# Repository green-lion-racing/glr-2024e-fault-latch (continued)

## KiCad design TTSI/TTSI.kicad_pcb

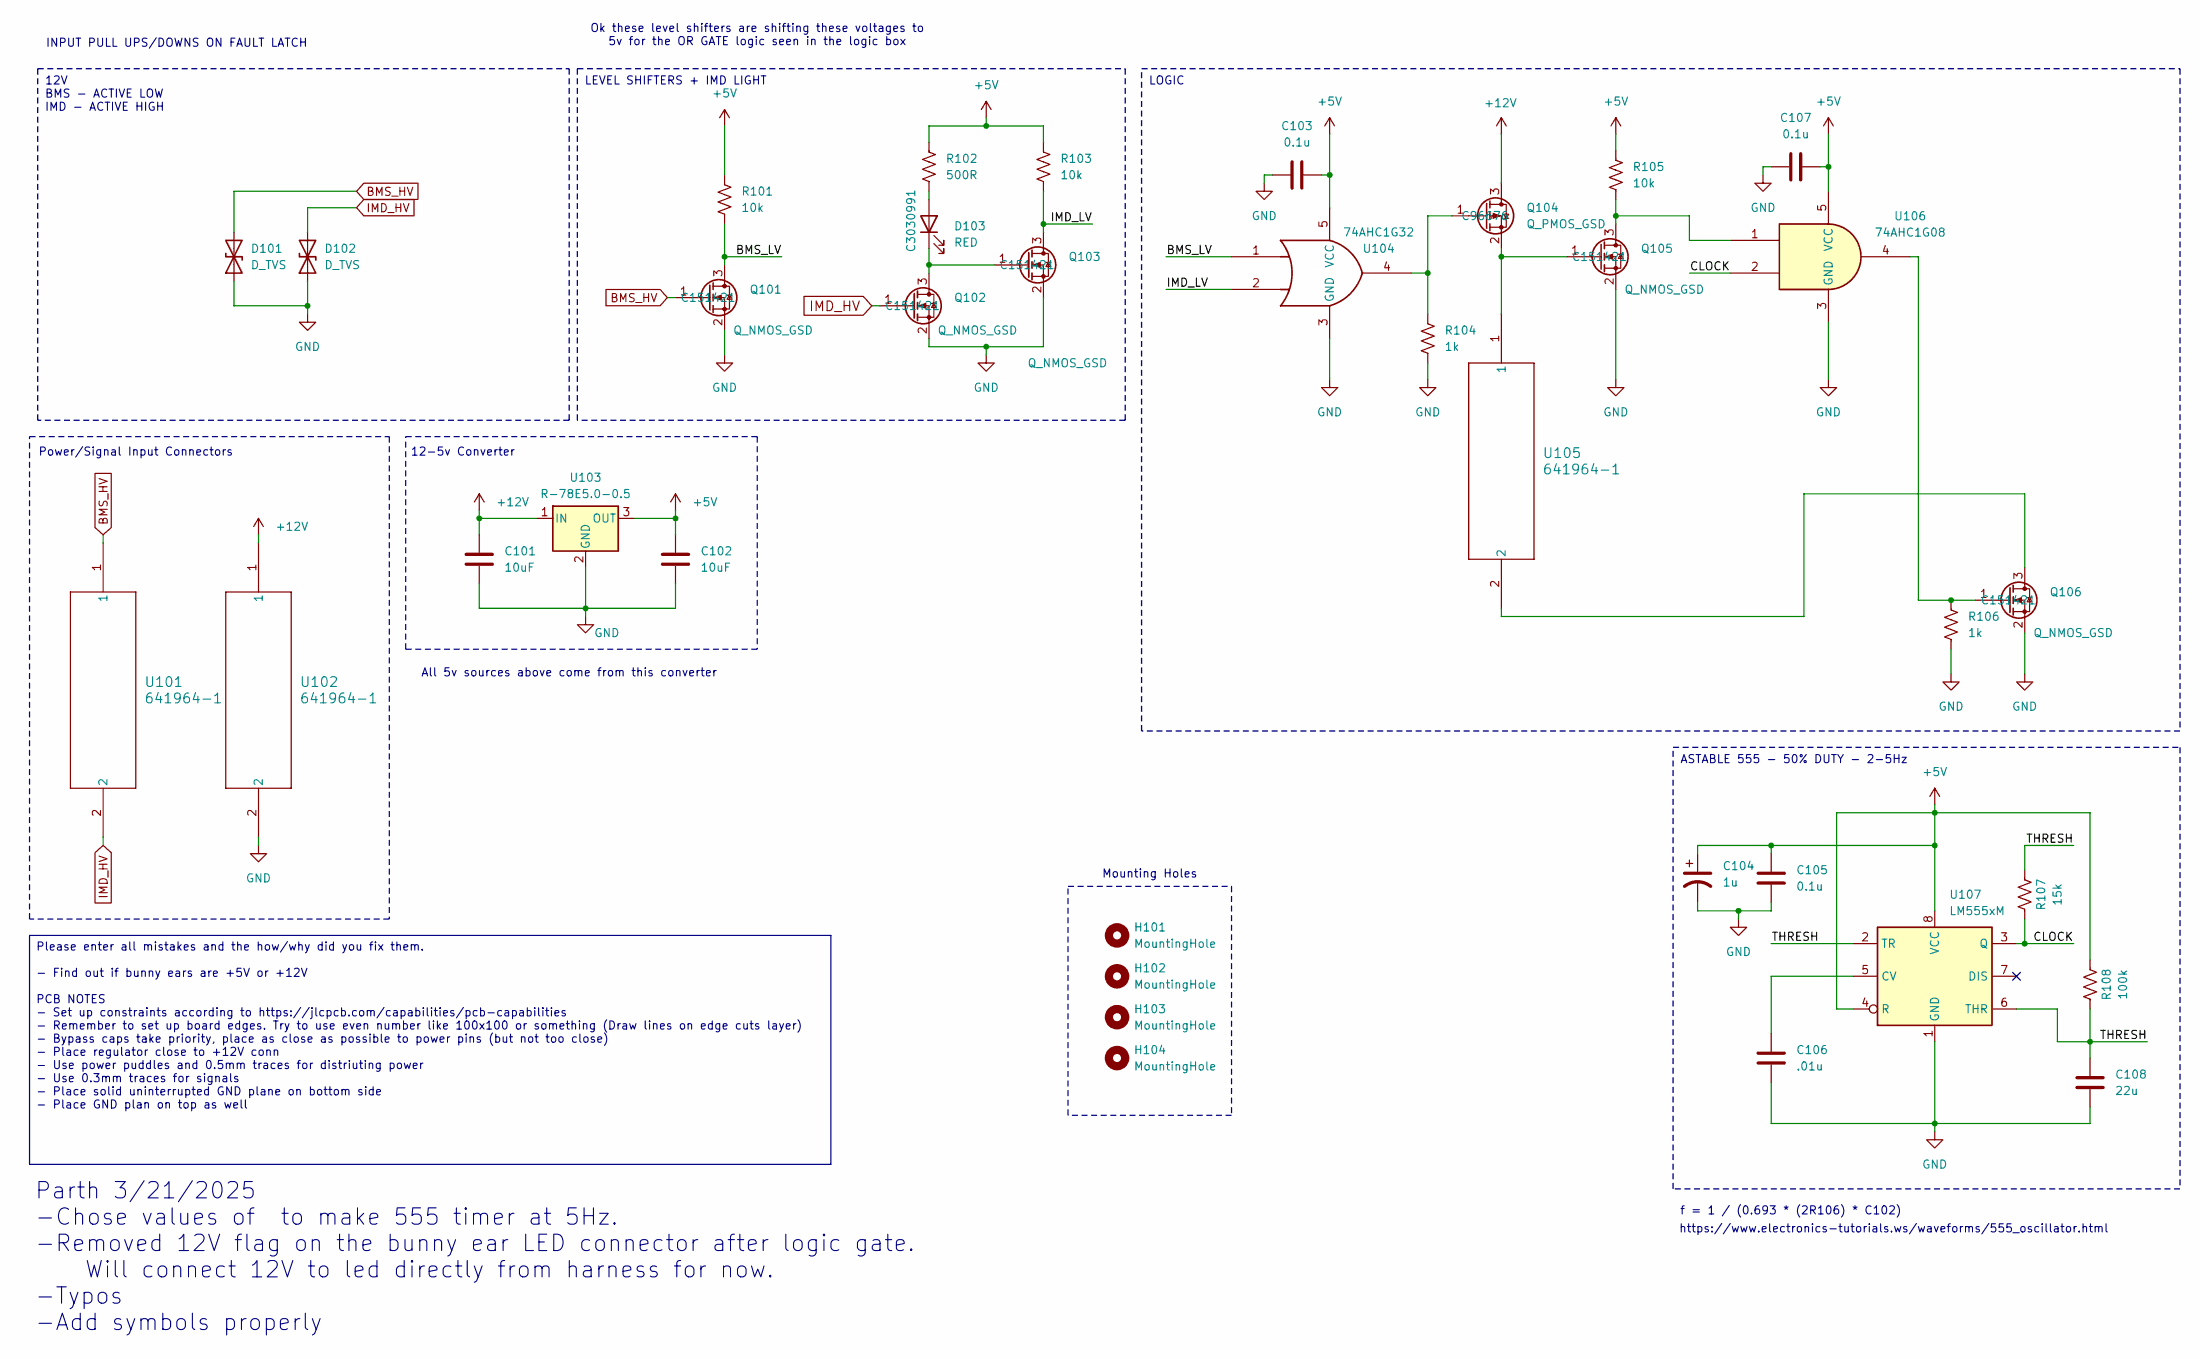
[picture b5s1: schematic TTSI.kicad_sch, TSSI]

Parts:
C101, C102: 10uF; C_0402_1005Metric; JLC# C307520
C103, C105, C107: 0.1u; C_0402_1005Metric; JLC# C133086
C104: 1u; C_0402_1005Metric; JLC# C59782
C106: .01u; C_0402_1005Metric; JLC# C15195
C108: 22u; C_0402_1005Metric
D101, D102: D_TVS; D_SOD-123F; JLC# C110748
D103: RED; R_0603_1608Metric; JLC# C3030991
H101, H102, H103, H104: MountingHole; MountingHole_2.2mm_M2
Q101, Q102, Q103, Q105, Q106: Q_NMOS_GSD; SOT-23; JLC# C151421
Q104: Q_PMOS_GSD; SOT-523; JLC# C96676
R101, R103, R105: 10k; R_0603_1608Metric; JLC# C130232
R102: 500R; R_0603_1608Metric; JLC# C130232
R104, R106: 1k; R_0603_1608Metric; JLC# C105637
R107: 15k; R_0603_1608Metric
R108: 100k; R_0603_1608Metric; JLC# C60491
U101, U102, U105: 641964-1; 641964-1_TYC
U103: R-78E5.0-0.5; R-78E-0.5_RCP; JLC# C5199916
U104: 74AHC1G32; SOT-353_SC-70-5; JLC# C7394028
U106: 74AHC1G08; SOT-353_SC-70-5; JLC# C2861162
U107: LM555xM; SOIC-8_3.9x4.9mm_P1.27mm; JLC# C90760

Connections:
+5V: C102.1, C103.1, C104.1, C105.1, C107.1, R101.1, R102.1, R103.1, R105.1, R108.2, U103.3 (OUT), U104.5 (VCC), U106.5 (VCC), U107.4 (R), U107.8 (VCC)
+12V: C101.1, Q104.3 (D), U102.1, U103.1 (IN)
/BMS_LV: Q101.3 (D), R101.2, U104.1
/CLOCK: R107.1, U106.2, U107.3 (Q)
/IMD_LV: Q103.3 (D), R103.2, U104.2
/THRESH: C108.2, R107.2, R108.1, U107.2 (TR), U107.6 (THR)
BMS_HV: D101.2 (A2), Q101.1 (G), U101.1
GND: C101.2, C102.2, C103.2, C104.2, C105.2, C106.2, C107.2, C108.1, D101.1 (A1), D102.1 (A1), Q101.2 (S), Q102.2 (S), Q103.2 (S), Q105.2 (S), Q106.2 (S), R104.2, R106.2, U102.2, U103.2 (GND), U104.3 (GND), U106.3 (GND), U107.1 (GND)
IMD_HV: D102.2 (A2), Q102.1 (G), U101.2
unnamed: D103.2 (A), R102.2
unnamed: D103.1 (K), Q102.3 (D), Q103.1 (G)
unnamed: Q104.1 (G), R104.1, U104.4
unnamed: Q104.2 (S), Q105.1 (G), U105.1
unnamed: Q105.3 (D), R105.2, U106.1
unnamed: Q106.3 (D), U105.2
unnamed: Q106.1 (G), R106.1, U106.4
unnamed: C106.1, U107.5 (CV)

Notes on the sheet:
Mounting Holes
All 5v sources above come from this converter
f = 1 / (0.693 * (2R106) * C102)
INPUT PULL UPS/DOWNS ON FAULT LATCH
Power/Signal Input Connectors
Parth 3/21/2025 -Chose values of to make 555 timer at 5Hz. -Removed 12V flag on the bunny ear LED connector after logic gate. Will connect 12V to led directly from harness for now. -Typos -Add symbols properly
Ok these level shifters are shifting these voltages to 5v for the OR GATE logic seen in the logic box
12-5v Converter
https://www.electronics-tutorials.ws/waveforms/555_oscillator.html
LEVEL SHIFTERS + IMD LIGHT
ASTABLE 555 - 50% DUTY - 2-5Hz
LOGIC
12V BMS - ACTIVE LOW IMD - ACTIVE HIGH
Please enter all mistakes and the how/why did you fix them. - Find out if bunny ears are +5V or +12V PCB NOTES - Set up constraints according to https://jlcpcb.com/capabilities/pcb-capabilities - Remember to set up board edges. Try to use even number like 100x100 or something (Draw lines on edge cu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

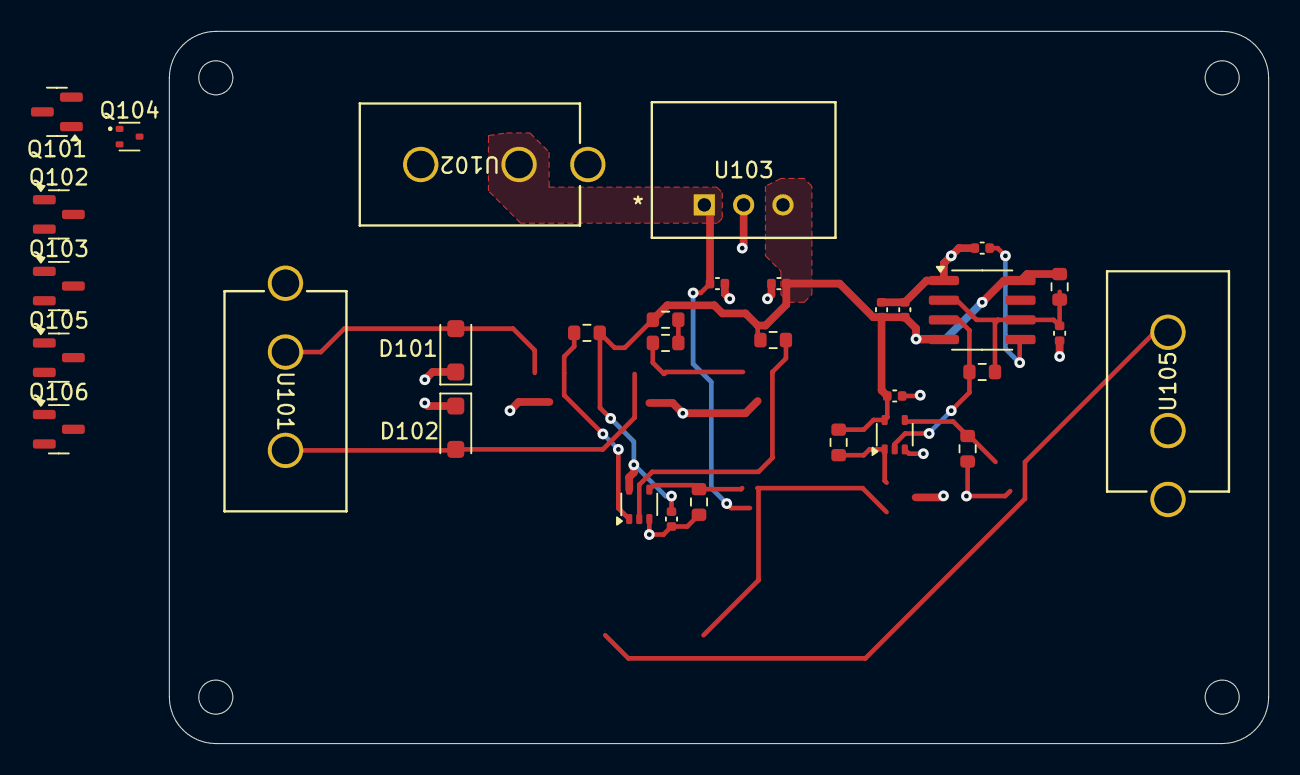
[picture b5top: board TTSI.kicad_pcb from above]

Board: 2 copper layers, 71.0 x 46.0 mm, 36 parts (0 on the bottom side), 17 nets.

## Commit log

2025-02-12 Test commit 2
2025-02-12 BSPD First Commit
2025-02-13 Fixed one logical error. Added LT Spice simulation. Pullup Caps, resistor values, schematic layout and cleanup needed.
2025-02-15 Added Current work on Fault Latch
2025-02-15 File Organization
2025-02-19 A - in README
2025-02-19 TTSI
2025-02-19 To Dos on Fault Latch and RML AGAIN.
2025-02-19 TSSI FIXES
2025-02-19 Improved TSSI
2025-02-19 TSSI BOM and BYPASS
2025-02-21 Unfinished version of Fault Latch after applying separate circuits
2025-02-21 Fault Latch Revision without PSpice Check
2025-02-21 RML Fixes
2025-02-21 Comments on BSPD, TSSI
2025-02-22 Added theory of operation to BSPD
2025-02-24 Edits to Fault Latch and TSSI
2025-02-25 Edits to RML
2025-02-26 RML Connectors
2025-03-01 Create TSSI MASON's changes
2025-03-01 Update TSSI MASON's changes
2025-03-02 Added series resistor to RML
2025-03-02 Added footprints,implemented changes from meeting, starting layout
2025-03-02 Updating footprints
2025-03-08 Fixed the logic for IMD and BSPD
2025-03-09 Added some footprints but also realized stuff about rules we need to change fault latch for
2025-03-11 TSSI Update
2025-03-11 Fixed directory issues
2025-03-11 RML changes
2025-03-12 RML Notes
2025-03-12 TSSI and FL fixes
2025-03-12 Added the pulse generators for the buttons
2025-03-16 Few changes to BOM as well as added 12v to bunny ears
2025-03-17 Added decoup capacitor
2025-03-18 Fault Latch Overhaul
2025-03-21 add useful commit messages they say
2025-03-21 R,C values for 555. Layout start
2025-03-21 notes
2025-03-22 Layout, routing, footprint addition, constraints set. Some component nets might be too small idk. But needs revision
2025-03-22 Connector changes, layout, edge cuts, constraints. Need advice on output PMOS
2025-03-23 Bypass caps bspd
2025-03-26 Redone logic for BSPD.
2025-03-26 Layout
2025-03-28 Tried to do traces of Fault Latch
2025-03-28 RML footprints
2025-03-30 NO ERROR FAULT LATCH.
2025-03-30 Found jlcpart for dcdc converter. It's chinese
2025-03-30 Broken pcb
2025-04-01 Not correct footprints...need to change later.
2025-04-03 Changes to RML and TSSI
2025-04-07 showed an error on the fault latch
2025-04-08 Charging Schematic/PCB v1
2025-04-08 Updated Charging PCB Layout
2025-04-08 Fixed bad folder
2025-04-09 unfinished connector addition to schematic
2025-04-10 Removed bad File
2025-04-10 added connectors, relay traces, mounting holes, labels
2025-04-11 cleaned up fault latch a little
2025-04-11 Fillet edges, shrunk relay traces, fixed labels for vinh
2025-04-12 Finished all part#'s. generated gerber and BOM files
2025-04-15 minor updates to fault latch and RML pcb layout
2025-04-15 Compacted PCB, and finished BOM,CPL,Gerbers(Charging)
2025-04-15 Added changes to RML and re-routed to fit on 1 layer
2025-04-15 Updated RML BOM
2025-04-15 JLC PCB BOM, placement redone to account for footprint changes, started re-routing
2025-04-15 Routing, final BOM
2025-04-15 Fixed some errors on TSSI
2025-04-15 Fixed RML footprint issues
2025-04-15 Fixed TSSI footprint issues
2025-04-16 redid tssi layout
2025-04-16 BSPD Fixes
2025-04-16 Fixed bad PMOS footprint and symbol, fixed gerbers/BOM/CPL
2025-04-16 resolved DRC errors for via sizes and footprints.
    via size changed to 6mm/3mm should still work for JLC. Connected unconnected items. Changed footprints to fix overlap issue
2025-04-17 TSSI has been integrated into fault latch.
2025-04-17 Almost complete merge of fault latch and tssi, footprint still not working for PMOS
2025-04-18 FIXED PMOS
2025-04-18 Fault Latch V2.0 Prototype
2025-04-18 Fault Latch V2.0 waiting for final check
2025-04-19 BSPD needs to be fixed + Fault Latch Layout Issue
2025-04-19 Fault latch added Logo
2025-04-19 RML READY
2025-04-19 FAULT LATCH CHANGES
2025-04-19 Fixed Fault Latch Layout
2025-04-19 Fault latch BOM
2025-04-19 generated gerber files
2025-04-19 BSPD READY
2025-04-19 CHARGE READY
2025-04-19 FL READY
2025-04-19 Finished schematic with added SR latch and new buttons, started layout
2025-04-19 Rerouted for grounding
2025-04-19 Double checked PMOS output logic. Added connector and routing for sense wires from sensors. Connected one unconnected track. 2 DRC errors about spokes, but otherwise Ready to Geaux :3
2025-04-21 Added SR Latch to charging PCB, completed gerbers,bom,and CPL file and added mouser parts list to assembly file
2025-04-21 Fault Latch Updated and generated gerber files
2025-04-22 Added charging wiring schematic with wire gauges for connection to accumulator
2025-04-22 Fixed gerbers for RML and FaultLatch
2025-04-22 Labeling for clarithy
2025-04-23 BSPD now active low output, fault latch rerouted.
2025-04-23 Manufacturing generated for BSPD and Fault Latch
2025-04-23 Double checked schematic. Fixed wrong connection on comparators and did re-routed the signals. Added new simulation with 555 timer and double cchecked that it is active low performing
2025-05-12 Updated BOM
2025-06-03 ESF documentation and wiring schematics for charging
2025-06-11 initial fork
    remove everything except fault latch stuff
2025-06-11 rename project to glr-2024e-fault-latch
2025-06-12 work in progress
    keep only bms and imd
    remove tssi stuff
2025-06-13 almost finished
    add bms light logic
    improve overall placements of components
    improve routing
    improve silk component identifiers
2025-06-13 add details
    add license
2025-06-13 update README.md
    add JacobParent7 as creator
2025-06-13 add glr logo
2025-06-17 use to screw terminals
    improve labels in schematic
2025-06-17 clean up tracks and vias
2025-06-17 add .pdf files to .gitignore
2025-06-17 change output directory
